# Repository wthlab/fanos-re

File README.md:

# fanos-re

This is a reverse engineered schematic of fanos 9W LED light bulb controller. Some of the components value were missing and will be added later. The main controller for this board is BP2832K and you may find the BP2832A datasheet in this repository.

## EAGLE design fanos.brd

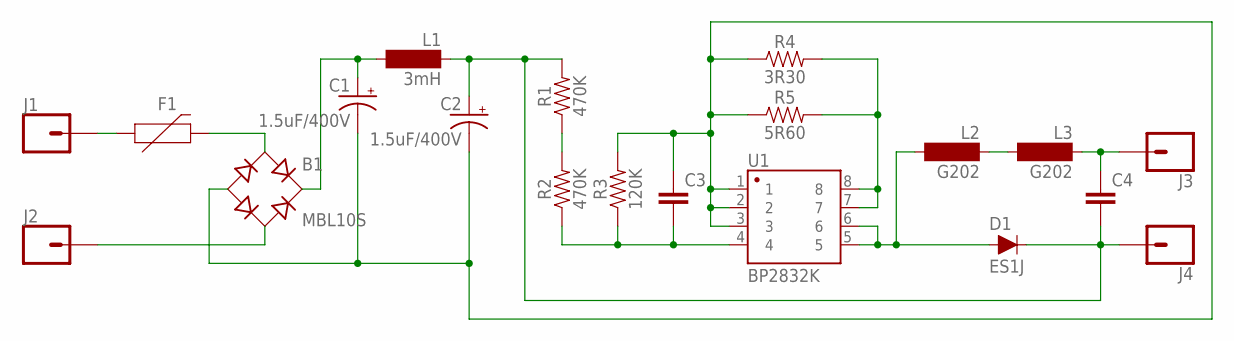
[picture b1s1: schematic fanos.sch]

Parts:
B1: MBL10S; SOIC-4
C1, C2: 1.5uF/400V; CPOL-RADIAL-5MM-10MM
C3: 0.18UF-0603-10V-10%; 0603
C4: 0.33UF/330NF-0805-50V-10%; 0805
D1: ES1J; SOD-323
F1: PPTC_PTH; PTH
J1, J2, J3, J4: CONN_01; 1X01
L1: 3mH; BS11
L2, L3: G202; BS11
R1, R2: 470K; 0805
R3: 120K; 0603
R4: 3R30; 1210
R5: 5R60; 1210
U1: BP2832K; SO08

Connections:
unnamed: B1.~2 (AC2), J2.1
unnamed: F1.P$1 (1), J1.1
unnamed: B1.~1 (AC1), F1.P$2 (2)
unnamed: B1.-, C1.-, C2.-, C3.1, R3.2, R4.1, R5.1, U1.1, U1.2, U1.3
unnamed: B1.+, C1.+, L1.2
unnamed: C3.2, R2.1, R3.1, U1.4
unnamed: R1.1, R2.2
unnamed: R4.2, R5.2, U1.7, U1.8
unnamed: D1.A, L2.2, U1.5, U1.6
unnamed: C2.+, C4.2, D1.C, J4.1, L1.1, R1.2
unnamed: L2.1, L3.2
unnamed: C4.1, J3.1, L3.1

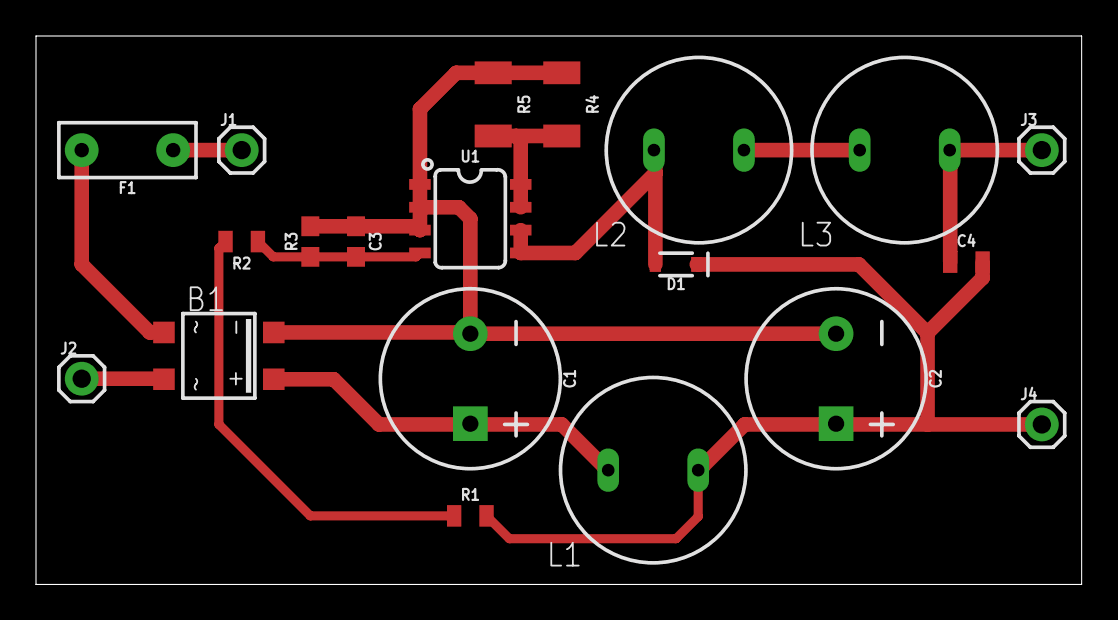
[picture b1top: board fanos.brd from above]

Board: 2 copper layers, 58.1 x 30.5 mm, 20 parts (0 on the bottom side), 12 nets.

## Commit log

2017-11-25 Added schematics and datasheet
2017-11-26 Fixed some wiring and added board layout

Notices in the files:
parts and their libraries:
SparkFun-Capacitors: Licensing: Creative Commons ShareAlike 4.0 International - https://creativecommons.org/licenses/by-sa/4.0
